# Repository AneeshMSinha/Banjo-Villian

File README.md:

# Banjo-Villian

A (work in Progress) ripoff of guitar hero

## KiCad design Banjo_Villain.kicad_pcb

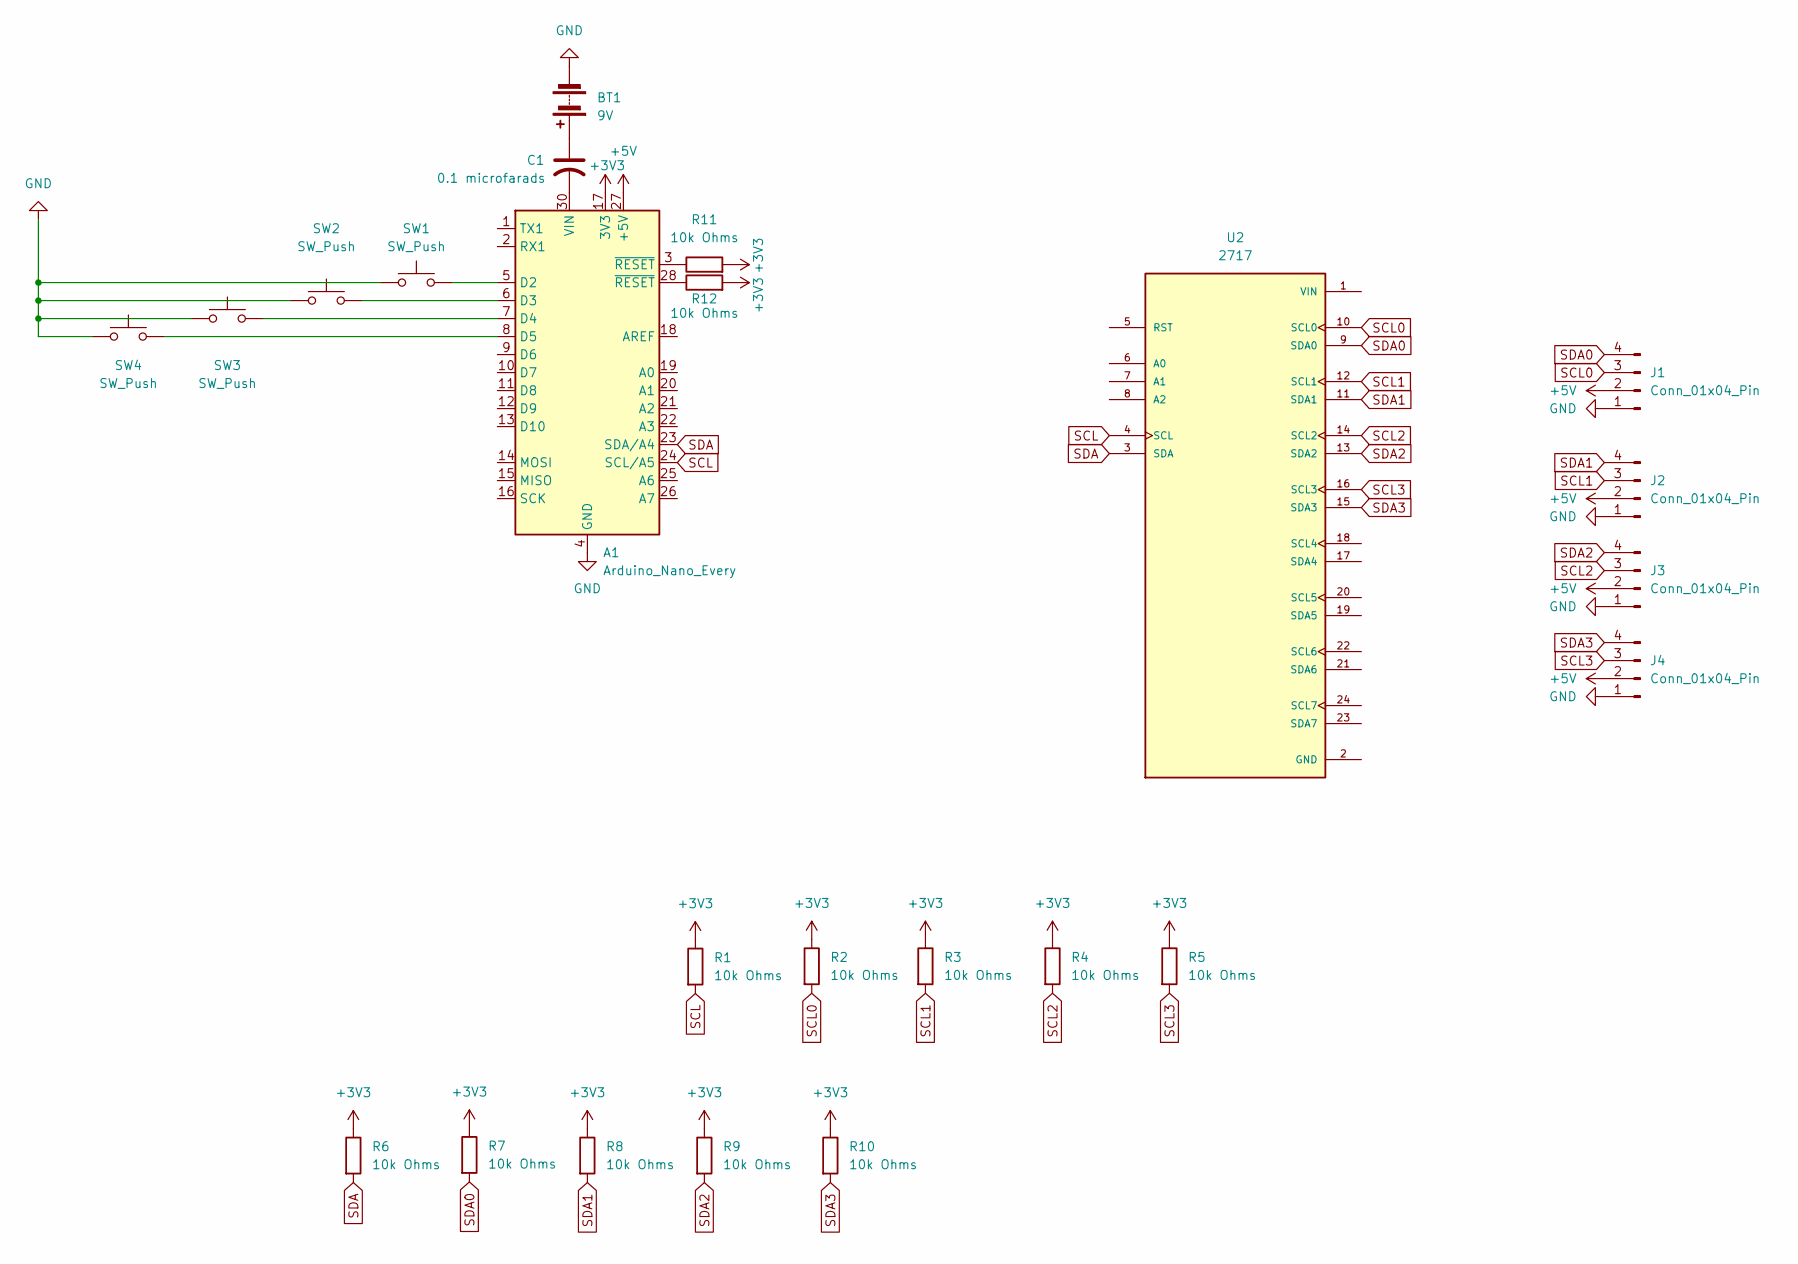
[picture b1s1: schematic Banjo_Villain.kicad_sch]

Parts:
A1: Arduino_Nano_Every; Arduino_Nano
BT1: 9V; BatteryHolder_MPD_BA9VPC_1xPP3
C1: 0.1 microfarads; C_0402_1005Metric
J1, J2, J3, J4: Conn_01x04_Pin; SSD1306-0.91-OLED-4pin-128x32
R1, R2, R3, R4, R5, R6, R7, R8, R9, R10, R11, R12: 10k Ohms; R_0805_2012Metric
SW1, SW2, SW3, SW4: SW_Push; SW_Cherry_MX_1.00u_PCB
U2: 2717; MODULE_2717; PARTREV Sep 11, 2015

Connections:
+3V3: A1.17 (3V3), R1.1, R2.1, R3.1, R4.1, R5.1, R6.1, R7.1, R8.1, R9.1, R10.1, R11.2, R12.2
+5V: A1.27 (+5V), J1.2, J2.2, J3.2, J4.2
GND: A1.4 (GND), A1.29 (GND), BT1.2 (-), J1.1, J2.1, J3.1, J4.1, SW1.1, SW2.1, SW3.1, SW4.1
unnamed: A1.5 (D2), SW1.2
unnamed: A1.6 (D3), SW2.2
unnamed: A1.7 (D4), SW3.2
unnamed: A1.8 (D5), SW4.2
unnamed: A1.30 (VIN), C1.2
unnamed: A1.3 (~RESET), R11.1
unnamed: A1.28 (~RESET), R12.1
unnamed: BT1.1 (+), C1.1
SCL: A1.24 (SCL/A5), R1.2, U2.4 (SCL)
SCL0: J1.3, R2.2, U2.10 (SCL0)
SCL1: J2.3, R3.2, U2.12 (SCL1)
SCL2: J3.3, R4.2, U2.14 (SCL2)
SCL3: J4.3, R5.2, U2.16 (SCL3)
SDA: A1.23 (SDA/A4), R6.2, U2.3 (SDA)
SDA0: J1.4, R7.2, U2.9 (SDA0)
SDA1: J2.4, R8.2, U2.11 (SDA1)
SDA2: J3.4, R9.2, U2.13 (SDA2)
SDA3: J4.4, R10.2, U2.15 (SDA3)

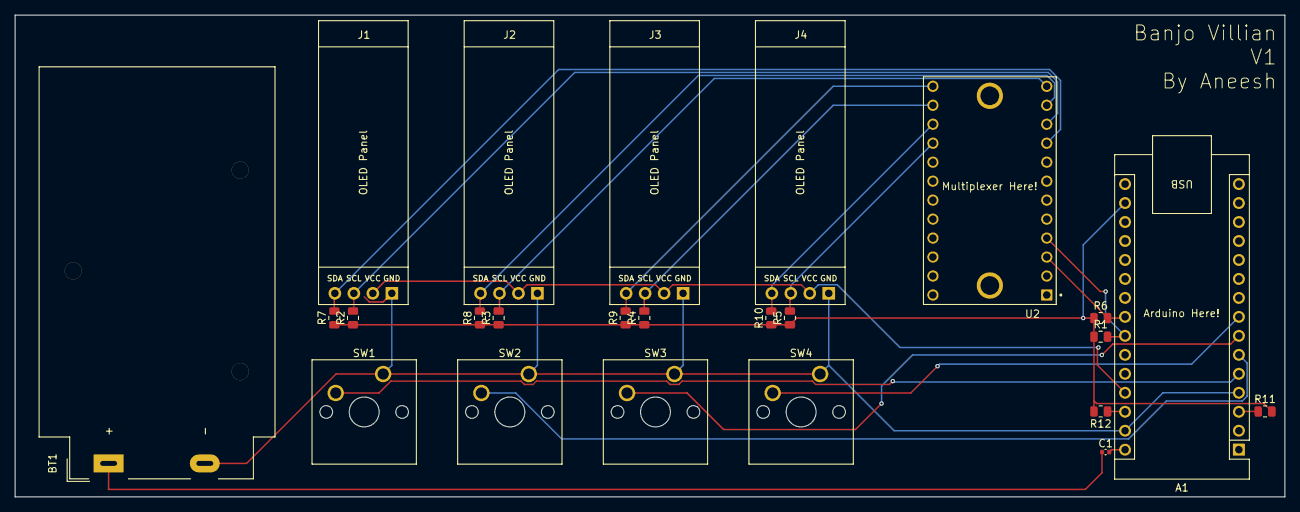
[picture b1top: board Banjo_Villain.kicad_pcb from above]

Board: 2 copper layers, 170.0 x 64.5 mm, 24 parts (0 on the bottom side), 21 nets.

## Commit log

2026-05-26 added KiCad filles
2026-05-26 Created a Test file to move stuff into folders
2026-05-26 moved files
2026-05-26 Create Test File
2026-05-26 Rename Banjo_Villain.kicad_pcb to Banjo_Villain.kicad_pcb
2026-05-26 Rename Banjo_Villain.kicad_sch to Hardware/KiCad Files/Banjo_Villain.kicad_sch
2026-05-26 Update Test
2026-05-27 Added Case Files
2026-05-27 Rename Case Bottom.step to Hardware/Onshape Files/Case Bottom.step
2026-05-27 Rename Case top.step to Hardware/Onshape Files/Case top.step
2026-05-27 Created Onshape source
